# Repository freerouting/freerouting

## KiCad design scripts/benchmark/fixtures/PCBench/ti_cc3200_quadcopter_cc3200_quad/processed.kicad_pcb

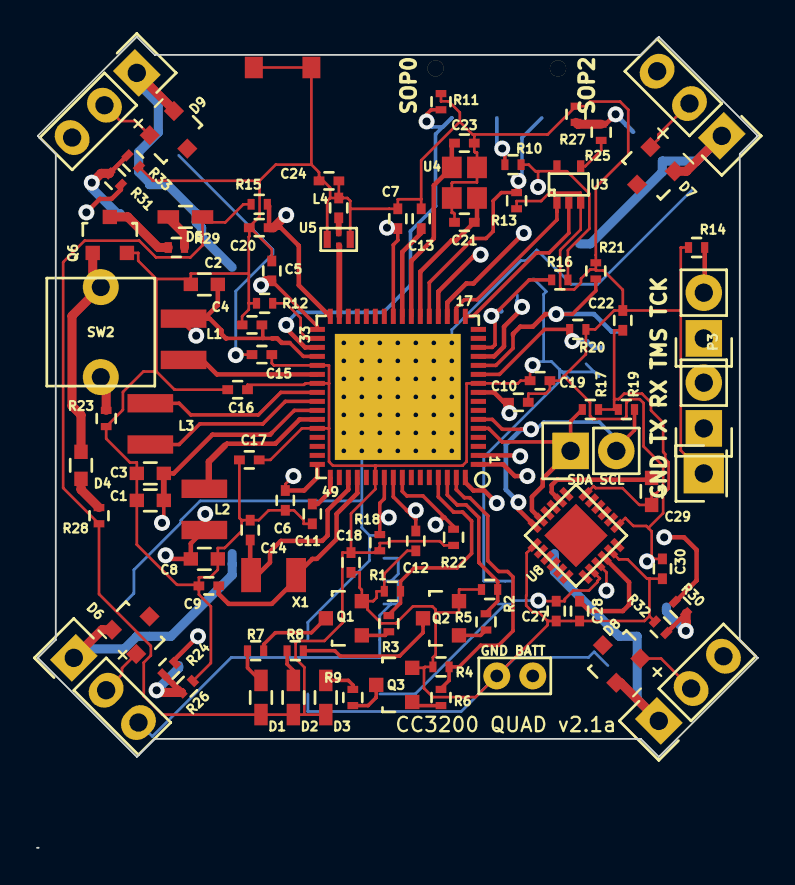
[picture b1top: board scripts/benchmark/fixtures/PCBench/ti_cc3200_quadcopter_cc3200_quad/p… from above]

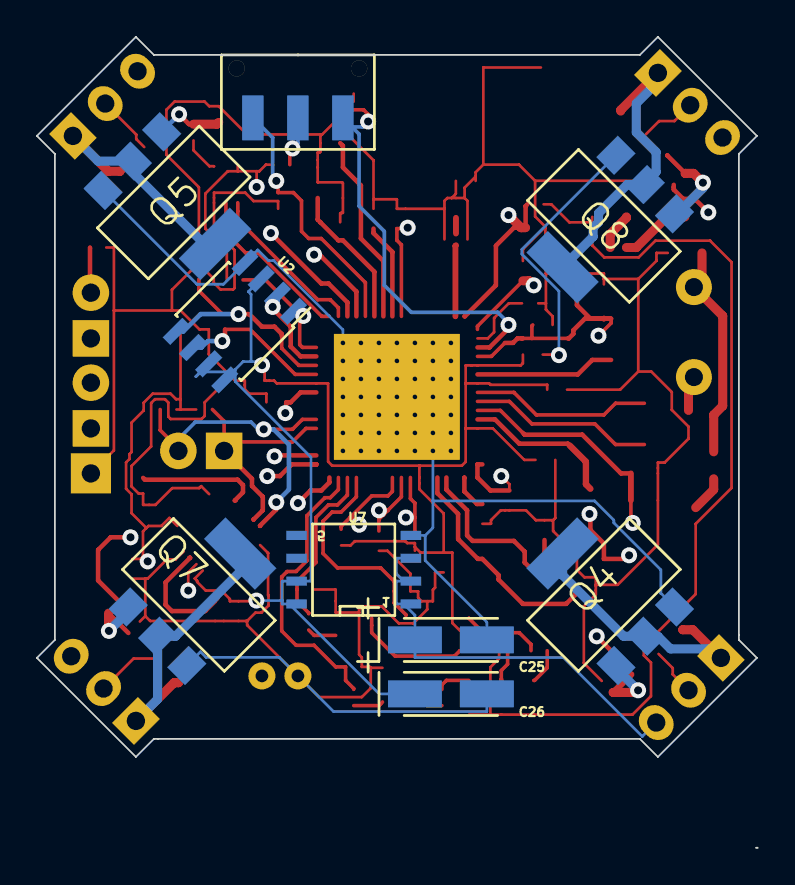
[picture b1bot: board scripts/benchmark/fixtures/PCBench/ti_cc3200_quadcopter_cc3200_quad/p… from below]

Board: 4 copper layers, 40.0 x 40.0 mm, 104 parts (9 on the bottom side), 65 nets.

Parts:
BT1: JST_CONNECTOR; JST_2PIN_2mm
C1, C3: 22uF; C_0603
C2, C8: 10uF; C_0603
C4, C5, C6, C7, C10, C11, C12, C13, C18, C19, C20, C22, C28, C30: 0.1uF; C_0402
C9, C14: 10pF; C_0402
C15, C16, C17: 4.7uF; C_0402
C21, C23: 6.2pF; C_0402
C24: 1.0pF; C_0402
C25, C26: 100uF; TantalC_SizeA_EIA-3216_HandSoldering
C27: 10nF; C_0402
C29: 2.2nF; C_0603
D1, D2, D3, D5: LED; C_0603_HandSoldering
D4: CD0603-B00340; C_0603
D6, D7, D8, D9: BAT54; SOT-23
L1, L2: 2.2uH; Neosid_Inductor_SM-NE29_SMD1008
L3: 1uH; Neosid_Inductor_SM-NE29_SMD1008
L4: 3.6nH; C_0402
M1, M2, M3, M4: DC_Motor; Pin_Header_Straight_1x03
P1, P2, P3: CONN_01X02; Pin_Header_Straight_1x02
P4: CONN_01X01; Pin_Header_Straight_1x01
Q1, Q2, Q3, Q6: BSS138; SOT-23
Q4, Q5, Q7, Q8: BUK9832; SOT-223
R1, R2, R4, R11, R12, R14, R15, R16, R18, R20, R21, R22, R28: 100k; R_0402
R3, R5, R6: 10k; R_0402
R7, R8, R9, R10, R29: 270; R_0402
R13: 2.7k; R_0402
R17, R19: 1k; R_0402
R23: 100; R_0402
R24, R25, R30, R31: 150; R_0402
R26, R27, R32, R33: 1.5k; R_0402
SW1: SWITCH_INV; JS102011SAQN
SW2: EVQ11; EVQ11_Push_Switch
U1: CC3200; cc3200
U2: MX25V8006E; SOIC-8_3.9x4.9mm_Pitch1.27mm
U3: SN74AUP1T08; sc70-5
U4: Q24FA20H00396_40MHz; Q24FA20H
U5: DEA202450BT-1294C1-H; DEA202450BT
U6: AH316M245001; AH316M
U7: MCP1726; SOIC-8-N
U8: MPU6050; MPU-6050
X1: 32.768KHz; ABS07

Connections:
+3.3V: C15.1, C16.1, C17.1, C18.1, C19.1, C22.1, C26.1, C27.1, C30.1, D1.1, D2.1, D3.1, D5.1, R10.1, R15.1, R16.1, R17.1, R18.1, R19.1, R22.1, R28.1, U1.10, U1.37, U1.39, U1.44, U1.54, U2.3, U2.7, U2.8, U3.5, U7.7, U7.8, U8.8, U8.13
+BATT: BT1.1, C25.1, D6.2, D7.2, D8.2, D9.2, M1.2, M2.2, M3.2, M4.2, U7.1, U7.2, U7.3
/LED_1: R1.2, R3.2, U1.61
/LED_2: R2.2, R5.2, U1.62
/LED_3: R4.2, R6.2, U1.63
/Motor_PWM01: R24.2, U1.1
/Motor_PWM02: R30.2, U1.2
/Motor_PWM03: R25.2, U3.4
/Motor_PWM04: R31.2, U1.64
/cc3200_camera_RF/RF: U1.31, U5.1
/cc3200_quad_accel/SCL: P1.1, R17.2, U1.5, U8.23
/cc3200_quad_accel/SDA: P1.2, R19.2, U1.6, U8.24
/rx: P3.2, R22.2, U1.57
/tx: P3.1, R18.2, U1.55
/~Reset: C20.1, D4.2, Q6.1, R15.2, SW2.2, U1.32
GND: BT1.2, C1.2, C2.2, C3.2, C4.2, C5.2, C6.2, C7.2, C8.2, C9.2, C10.2, C11.2, C12.2, C13.2, C14.2, C15.2, C16.2, C17.2, C18.2, C19.2, C20.2, C21.2, C22.2, C23.2, C24.1, C24.2, C25.2, C26.2, C27.2, C28.2, C29.1, C30.2, L4.2, P4.1, Q1.2, Q2.2, Q3.2, Q4.3, Q5.3, Q6.2, Q7.3, Q8.3, R1.1, R2.1, R4.1, R11.2, R12.2, R13.2, R14.1, R20.1, R21.1, R23.2, R26.1, R27.1, R32.1, R33.1, U1.65, U2.4, U3.3, U4.2, U4.4, U5.2, U5.4, U6.1, U6.2, U7.4, U8.1, U8.9, U8.11, U8.18
unnamed: C1.1, C3.1, C5.1, U1.33, U1.42
unnamed: C2.1, C4.1, C6.1, C7.1, L1.1, U1.25, U1.36, U1.48
unnamed: C9.1, U1.52, X1.2
unnamed: C8.1, C10.1, C12.1, L2.1, U1.9, U1.56
unnamed: C11.1, U1.49
unnamed: C13.1, U1.24
unnamed: C14.1, U1.51, X1.1
unnamed: C21.1, U1.22, U4.3
unnamed: C23.1, U1.23, U4.1
unnamed: C28.1, U8.10
unnamed: C29.2, U8.20
unnamed: D1.2, R7.1
unnamed: D2.2, R8.1
unnamed: D3.2, R9.1
unnamed: D4.1, R28.2
unnamed: D5.2, R29.1
unnamed: D6.1, M1.1, Q4.2
unnamed: D7.1, M2.1, Q5.2
unnamed: D8.1, M3.1, Q7.2
unnamed: D9.1, M4.1, Q8.2
unnamed: L1.2, U1.38
unnamed: L2.2, U1.43
unnamed: L3.1, U1.41
unnamed: L3.2, U1.40
unnamed: L4.1, U5.3
unnamed: P2.1, U1.20
unnamed: P2.2, R14.2, U1.19
unnamed: Q1.1, R3.1
unnamed: Q1.3, R7.2
unnamed: Q2.1, R5.1
unnamed: Q2.3, R8.2
unnamed: Q3.1, R6.1
unnamed: Q3.3, R9.2
unnamed: Q4.1, R24.1, R26.2
unnamed: Q5.1, R25.1, R27.2
unnamed: Q6.3, R29.2
unnamed: Q7.1, R30.1, R32.2
unnamed: Q8.1, R31.1, R33.2
unnamed: R10.2, SW1.2
unnamed: R11.1, SW1.1, U1.35
unnamed: R12.1, U1.34
unnamed: R13.1, SW1.3, U1.21
unnamed: R16.2, U1.14, U2.1
unnamed: R20.2, U1.11, U2.6
unnamed: R21.2, U1.12, U2.5
unnamed: R23.1, SW2.1
unnamed: U1.13, U2.2
unnamed: U1.17, U3.2
unnamed: U1.18, U3.1

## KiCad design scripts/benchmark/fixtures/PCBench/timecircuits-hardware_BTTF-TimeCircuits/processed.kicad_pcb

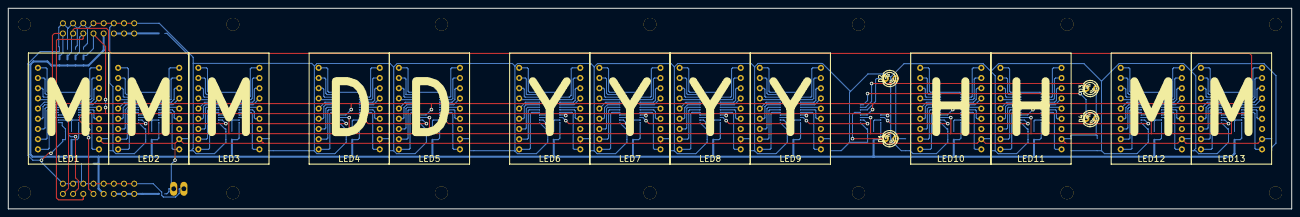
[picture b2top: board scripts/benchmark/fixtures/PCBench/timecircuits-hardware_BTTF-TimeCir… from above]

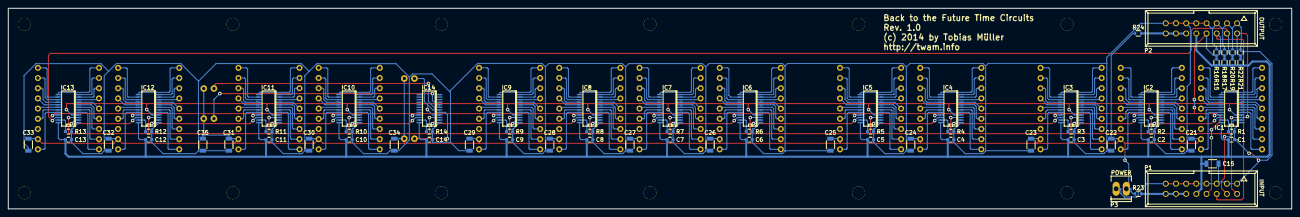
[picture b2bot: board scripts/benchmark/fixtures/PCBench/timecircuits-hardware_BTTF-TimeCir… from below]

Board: 2 copper layers, 320.0 x 50.0 mm, 102 parts (71 on the bottom side), 249 nets.

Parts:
C1, C2, C3, C4, C5, C6, C7, C8, C9, C10, C11, C12, C13, C14: C; C_0603
C15, C21, C22, C23, C24, C25, C26, C27, C28, C29, C30, C31, C32, C33, C34, C35: CP2; C_1206
D1, D2, D3, D4: LED; LED-3MM
IC1, IC2, IC3, IC4, IC5, IC6, IC7, IC8, IC9, IC10, IC11, IC12, IC13, IC14: TLC59284; SSOP-24
LED1, LED2, LED3, LED4, LED5, LED6, LED7, LED8, LED9, LED10, LED11, LED12, LED13: PSA08-11
MOUNTING_HOLE_3-2MM_M3, MOUNTING_HOLE_3-2MM_M3_2, MOUNTING_HOLE_3-2MM_M3_3, MOUNTING_HOLE_3-2MM_M3_4, MOUNTING_HOLE_3-2MM_M3_5, MOUNTING_HOLE_3-2MM_M3_6, MOUNTING_HOLE_3-2MM_M3_7, MOUNTING_HOLE_3-2MM_M3_8, MOUNTING_HOLE_3-2MM_M3_9, MOUNTING_HOLE_3-2MM_M3_10, MOUNTING_HOLE_3-2MM_M3_11, MOUNTING_HOLE_3-2MM_M3_12, MOUNTING_HOLE_3-2MM_M3_13, MOUNTING_HOLE_3-2MM_M3_14: VAL**; MOUNTING_HOLE_3-2MM_M3
P1: INPUT; VASCH8x2
P2: OUTPUT; VASCH8x2
P3: POWER; Socket_MOLEX-KK-RM2-54mm_Lock_2pin_straight
R1, R2, R3, R4, R5, R6, R7, R8, R9, R10, R11, R12, R13, R14: R; C_0603
R15, R16, R17, R18, R19, R20, R21, R22, R23, R24: R; R_0603

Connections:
+5V: C21.1, C22.1, C23.1, C24.1, C25.1, C26.1, C27.1, C28.1, C29.1, C30.1, C31.1, C32.1, C33.1, C34.1, C35.1, D1.1, D2.1, D3.1, D4.1, LED1.11, LED2.11, LED3.11, LED4.11, LED5.11, LED6.11, LED7.11, LED8.11, LED9.11, LED10.11, LED11.11, LED12.11, LED13.11, P3.1, R23.2, R24.2
/A1: IC1.13, LED1.1
/A2: IC2.13, LED2.1
/A3: IC3.13, LED3.1
/A4: IC4.13, LED4.1
/A5: IC5.13, LED5.1
/A6: IC6.13, LED6.1
/A7: IC7.13, LED7.1
/A8: IC8.13, LED8.1
/A9: IC9.13, LED9.1
/A10: IC10.13, LED10.1
/A11: IC11.13, LED11.1
/A12: IC12.13, LED12.1
/A13: IC13.13, LED13.1
/B1: IC1.14, LED1.18
/B2: IC2.14, LED2.18
/B3: IC3.14, LED3.18
/B4: IC4.14, LED4.18
/B5: IC5.14, LED5.18
/B6: IC6.14, LED6.18
/B7: IC7.14, LED7.18
/B8: IC8.14, LED8.18
/B9: IC9.14, LED9.18
/B10: IC10.14, LED10.18
/B11: IC11.14, LED11.18
/B12: IC12.14, LED12.18
/B13: IC13.14, LED13.18
/BLK: IC1.21, IC2.21, IC3.21, IC4.21, IC5.21, IC6.21, IC7.21, IC8.21, IC9.21, IC10.21, IC11.21, IC12.21, IC13.21, IC14.21, P1.8, P2.8, R15.2, R16.1
/C1: IC1.16, LED1.16
/C2: IC2.16, LED2.16
/C3: IC3.16, LED3.16
/C4: IC4.16, LED4.16
/C5: IC5.16, LED5.16
/C6: IC6.16, LED6.16
/C7: IC7.16, LED7.16
/C8: IC8.16, LED8.16
/C9: IC9.16, LED9.16
/C10: IC10.16, LED10.16
/C11: IC11.16, LED11.16
/C12: IC12.16, LED12.16
/C13: IC13.16, LED13.16
/D1: IC1.19, LED1.13
/D2: IC2.19, LED2.13
/D3: IC3.19, LED3.13
/D4: IC4.19, LED4.13
/D5: IC5.19, LED5.13
/D6: IC6.19, LED6.13
/D7: IC7.19, LED7.13
/D8: IC8.19, LED8.13
/D9: IC9.19, LED9.13
/D10: IC10.19, LED10.13
/D11: IC11.19, LED11.13
/D12: IC12.19, LED12.13
/D13: IC13.19, LED13.13
/DATA_IN: IC1.2, P1.4
/DATA_OUT: IC13.22, P2.4, R19.2, R20.1
/E1: IC1.20, LED1.10
/E2: IC2.20, LED2.10
/E3: IC3.20, LED3.10
/E4: IC4.20, LED4.10
/E5: IC5.20, LED5.10
/E6: IC6.20, LED6.10
/E7: IC7.20, LED7.10
/E8: IC8.20, LED8.10
/E9: IC9.20, LED9.10
/E10: IC10.20, LED10.10
/E11: IC11.20, LED11.10
/E12: IC12.20, LED12.10
/E13: IC13.20, LED13.10
/F1: IC1.5, LED1.9
/F2: IC2.5, LED2.9
/F3: IC3.5, LED3.9
/F4: IC4.5, LED4.9
/F5: IC5.5, LED5.9
/F6: IC6.5, LED6.9
/F7: IC7.5, LED7.9
/F8: IC8.5, LED8.9
/F9: IC9.5, LED9.9
/F10: IC10.5, LED10.9
/F11: IC11.5, LED11.9
/F12: IC12.5, LED12.9
/F13: IC13.5, LED13.9
/G1: IC1.6, LED1.8
/G2: IC2.6, LED2.8
/G3: IC3.6, LED3.8
/G4: IC4.6, LED4.8
/G5: IC5.6, LED5.8
/G6: IC6.6, LED6.8
/G7: IC7.6, LED7.8
/G8: IC8.6, LED8.8
/G9: IC9.6, LED9.8
/G10: IC10.6, LED10.8
/G11: IC11.6, LED11.8
/G12: IC12.6, LED12.8
/G13: IC13.6, LED13.8
/H1: IC1.10, LED1.4
/H2: IC2.10, LED2.4
/H3: IC3.10, LED3.4
/H4: IC4.10, LED4.4
/H5: IC5.10, LED5.4
/H6: IC6.10, LED6.4
/H7: IC7.10, LED7.4
/H8: IC8.10, LED8.4
/H9: IC9.10, LED9.4
/H10: IC10.10, LED10.4
/H11: IC11.10, LED11.4
/H12: IC12.10, LED12.4
/H13: IC13.10, LED13.4
/K1: IC1.11, LED1.3
/K2: IC2.11, LED2.3
/K3: IC3.11, LED3.3
/K4: IC4.11, LED4.3
/K5: IC5.11, LED5.3
/K6: IC6.11, LED6.3
/K7: IC7.11, LED7.3
/K8: IC8.11, LED8.3
/K9: IC9.11, LED9.3
/K10: IC10.11, LED10.3
/K11: IC11.11, LED11.3
/K12: IC12.11, LED12.3
/K13: IC13.11, LED13.3
/LAT: IC1.4, IC2.4, IC3.4, IC4.4, IC5.4, IC6.4, IC7.4, IC8.4, IC9.4, IC10.4, IC11.4, IC12.4, IC13.4, IC14.4, P1.6, P2.6, R17.2, R18.1
/M1: IC1.12, LED1.2
/M2: IC2.12, LED2.2
/M3: IC3.12, LED3.2
/M4: IC4.12, LED4.2
/M5: IC5.12, LED5.2
/M6: IC6.12, LED6.2
/M7: IC7.12, LED7.2
/M8: IC8.12, LED8.2
/M9: IC9.12, LED9.2
/M10: IC10.12, LED10.2
/M11: IC11.12, LED11.2
/M12: IC12.12, LED12.2
/M13: IC13.12, LED13.2
/N1: IC1.15, LED1.17
/N2: IC2.15, LED2.17
/N3: IC3.15, LED3.17
/N4: IC4.15, LED4.17
/N5: IC5.15, LED5.17
/N6: IC6.15, LED6.17
/N7: IC7.15, LED7.17
/N8: IC8.15, LED8.17
/N9: IC9.15, LED9.17
/N10: IC10.15, LED10.17
/N11: IC11.15, LED11.17
/N12: IC12.15, LED12.17
/N13: IC13.15, LED13.17
/P1: IC1.17, LED1.15
/P2: IC2.17, LED2.15
/P3: IC3.17, LED3.15
/P4: IC4.17, LED4.15
/P5: IC5.17, LED5.15
/P6: IC6.17, LED6.15
/P7: IC7.17, LED7.15
/P8: IC8.17, LED8.15
/P9: IC9.17, LED9.15
/P10: IC10.17, LED10.15
/P11: IC11.17, LED11.15
/P12: IC12.17, LED12.15
/P13: IC13.17, LED13.15
/R1: IC1.18, LED1.14
/R2: IC2.18, LED2.14
/R3: IC3.18, LED3.14
/R4: IC4.18, LED4.14
/R5: IC5.18, LED5.14
/R6: IC6.18, LED6.14
/R7: IC7.18, LED7.14
/R8: IC8.18, LED8.14
/R9: IC9.18, LED9.14
/R10: IC10.18, LED10.14
/R11: IC11.18, LED11.14
/R12: IC12.18, LED12.14
/R13: IC13.18, LED13.14
/S1: IC1.8, LED1.6
/S2: IC2.8, LED2.6
/S3: IC3.8, LED3.6
/S4: IC4.8, LED4.6
/S5: IC5.8, LED5.6
/S6: IC6.8, LED6.6
/S7: IC7.8, LED7.6
/S8: IC8.8, LED8.6
/S9: IC9.8, LED9.6
/S10: IC10.8, LED10.6
/S11: IC11.8, LED11.6
/S12: IC12.8, LED12.6
/S13: IC13.8, LED13.6
/SCLK: IC1.3, IC2.3, IC3.3, IC4.3, IC5.3, IC6.3, IC7.3, IC8.3, IC9.3, IC10.3, IC11.3, IC12.3, IC13.3, IC14.3, P1.2, P2.2, R21.2, R22.1
/T1: IC1.7, LED1.7
/T2: IC2.7, LED2.7
/T3: IC3.7, LED3.7
/T4: IC4.7, LED4.7
/T5: IC5.7, LED5.7
/T6: IC6.7, LED6.7
/T7: IC7.7, LED7.7
/T8: IC8.7, LED8.7
/T9: IC9.7, LED9.7
/T10: IC10.7, LED10.7
/T11: IC11.7, LED11.7
/T12: IC12.7, LED12.7
/T13: IC13.7, LED13.7
/U1: IC1.9, LED1.5
/U2: IC2.9, LED2.5
/U3: IC3.9, LED3.5
/U4: IC4.9, LED4.5
/U5: IC5.9, LED5.5
/U6: IC6.9, LED6.5
/U7: IC7.9, LED7.5
/U8: IC8.9, LED8.5
/U9: IC9.9, LED9.5
/U10: IC10.9, LED10.5
/U11: IC11.9, LED11.5
/U12: IC12.9, LED12.5
/U13: IC13.9, LED13.5
GND: C1.2, C2.2, C3.2, C4.2, C5.2, C6.2, C7.2, C8.2, C9.2, C10.2, C11.2, C12.2, C13.2, C14.2, C15.2, C21.2, C22.2, C23.2, C24.2, C25.2, C26.2, C27.2, C28.2, C29.2, C30.2, C31.2, C32.2, C33.2, C34.2, C35.2, IC1.1, IC2.1, IC3.1, IC4.1, IC5.1, IC6.1, IC7.1, IC8.1, IC9.1, IC10.1, IC11.1, IC12.1, IC13.1, IC14.1, P1.1, P1.3, P1.5, P1.7, P1.9, P1.11, P1.13, P1.15, P2.1, P2.3, P2.5, P2.7, P2.9, P2.11, P2.13, P2.15, P3.2, R1.2, R2.2, R3.2, R4.2, R5.2, R6.2, R7.2, R8.2, R9.2, R10.2, R11.2, R12.2, R13.2, R14.2, R16.2, R18.2, R20.2, R22.2
unnamed: D1.2, IC14.5
unnamed: D2.2, IC14.6
unnamed: D3.2, IC14.7
unnamed: D4.2, IC14.8
unnamed: IC1.22, IC2.2
unnamed: IC1.23, R1.1
unnamed: IC2.22, IC3.2
unnamed: IC2.23, R2.1
unnamed: IC3.22, IC4.2
unnamed: IC3.23, R3.1
unnamed: IC4.22, IC5.2
unnamed: IC4.23, R4.1
unnamed: IC5.22, IC6.2
unnamed: IC5.23, R5.1
unnamed: IC6.22, IC7.2
unnamed: IC6.23, R6.1
unnamed: IC7.22, IC8.2
unnamed: IC7.23, R7.1
unnamed: IC8.22, IC9.2
unnamed: IC8.23, R8.1
unnamed: IC9.23, R9.1
unnamed: IC10.2, IC14.22
unnamed: IC10.22, IC11.2
unnamed: IC10.23, R10.1
unnamed: IC11.22, IC12.2
unnamed: IC11.23, R11.1
unnamed: IC12.22, IC13.2
unnamed: IC12.23, R12.1
unnamed: IC13.23, R13.1
unnamed: IC9.22, IC14.2
unnamed: IC14.23, R14.1
unnamed: P1.12, P1.14, P1.16, R23.1
unnamed: P2.12, P2.14, P2.16, R24.1
VCC: C1.1, C2.1, C3.1, C4.1, C5.1, C6.1, C7.1, C8.1, C9.1, C10.1, C11.1, C12.1, C13.1, C14.1, C15.1, IC1.24, IC2.24, IC3.24, IC4.24, IC5.24, IC6.24, IC7.24, IC8.24, IC9.24, IC10.24, IC11.24, IC12.24, IC13.24, IC14.24, P1.10, P2.10, R15.1, R17.1, R19.1, R21.1

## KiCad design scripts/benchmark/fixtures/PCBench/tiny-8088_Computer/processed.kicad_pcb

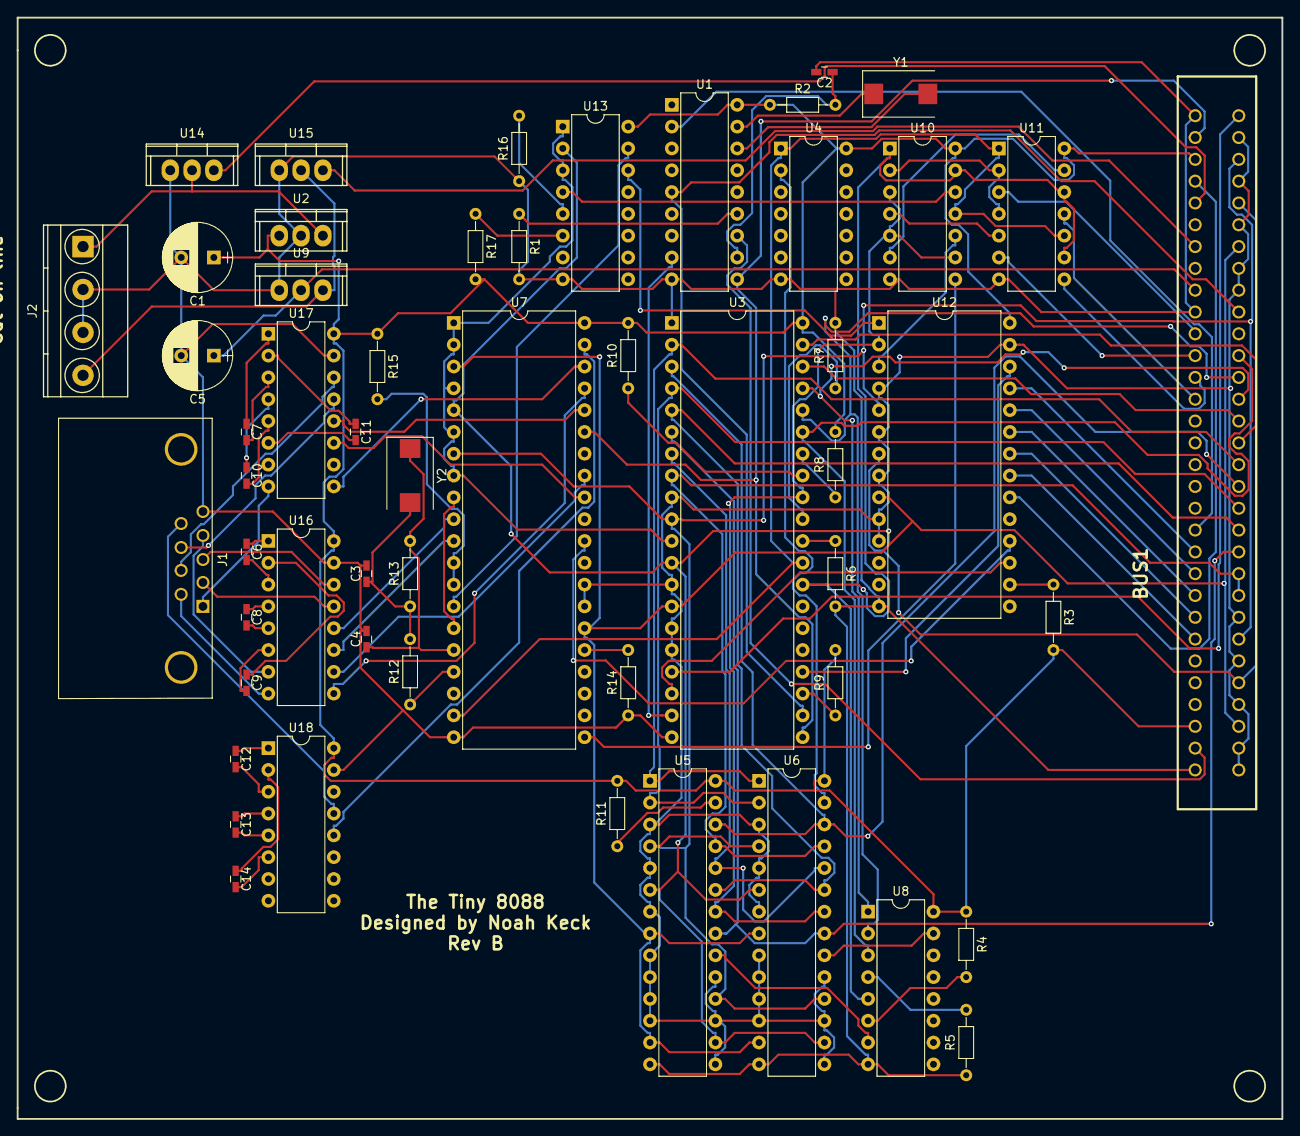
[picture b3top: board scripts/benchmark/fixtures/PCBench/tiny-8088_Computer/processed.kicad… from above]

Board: 2 copper layers, 147.3 x 128.3 mm, 54 parts (0 on the bottom side), 111 nets.

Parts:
BUS1: BUSPC; ISA8
C1, C5: 10 uF; CP_Radial_D8.0mm_P3.80mm
C2: 1n; C_0603_HandSoldering
C3, C4: 10 pF; C_0603_HandSoldering
C6, C7, C8, C9, C10, C11, C12, C13, C14: 1 uF; C_0603_HandSoldering
J1: DB9; DB9FC
J2: Screw_Terminal_1x04; TerminalBlock_Pheonix_MKDS1.5-4pol
R1, R3, R4, R5, R6, R7, R8, R9, R10, R11, R14, R15, R16, R17: 10k; R_Axial_DIN0204_L3.6mm_D1.6mm_P7.62mm_Horizontal
R2: 1k; R_Axial_DIN0204_L3.6mm_D1.6mm_P7.62mm_Horizontal
R12, R13: 2.2k; R_Axial_DIN0204_L3.6mm_D1.6mm_P7.62mm_Horizontal
U1: 8284; DIP-18_W7.62mm
U2: LM2931AZ-5.0; TO-220
U3: 8088; DIP-40_W15.24mm
U4, U10: 74LS04; DIP-14_W7.62mm
U5: 28C256; DIP-28_W7.62mm
U6: RAM_32KO; DIP-28_W7.62mm
U7: 16450; DIP-40_W15.24mm
U8, U13: 74LS138; DIP-16_W7.62mm
U9: NCP1117DT12G; TO-220
U11: 7400; DIP-14_W7.62mm
U12: 8259; DIP-28_W15.24mm
U14: LM7905CT; TO-220
U15: LM7912CT; TO-220
U16, U17, U18: MAX202; DIP-16_W7.62mm
Y1: 8 MHz; Crystal_SMD_FOX_FE-2pin_7.5x5.0mm
Y2: 3.072 MHz; Crystal_SMD_FOX_FE-2pin_7.5x5.0mm

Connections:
A0: BUS1.33, BUS1.35, BUS1.37, BUS1.39, BUS1.40, BUS1.55, BUS1.57, BUS1.59, BUS1.61, BUS1.62, U3.9, U3.11, U3.13, U3.15, U3.16, U5.3, U5.5, U5.7, U5.9, U5.10, U5.11, U5.12, U5.15, U5.17, U5.19, U6.3, U6.5, U6.7, U6.9, U6.10, U6.11, U6.12, U6.15, U6.17, U6.19, U7.1, U7.2, U7.4, U7.6, U7.8, U7.27, U7.28, U12.4, U12.6, U12.8, U12.10, U12.11, U12.27, U13.1, U13.3
A2: BUS1.38, BUS1.60, U3.14, U5.8, U5.13, U6.8, U6.13, U7.3, U7.26, U12.9
A4: BUS1.36, BUS1.58, U3.12, U5.6, U5.16, U6.6, U6.16, U7.5, U12.7, U13.2
A6: BUS1.34, BUS1.56, U3.10, U5.4, U5.18, U6.4, U6.18, U7.7, U12.5
A8: BUS1.53, BUS1.54, U3.8, U5.25, U6.25
A10: BUS1.52, U3.6, U5.21, U6.21
A11: BUS1.51, U3.5, U5.23, U6.23
A12: BUS1.50, U3.4, U5.2, U6.2
A13: BUS1.49, U3.3, U5.26, U6.26
A14: BUS1.48, U3.2, U5.1, U6.1
A15: BUS1.47, U3.39
A16: BUS1.46, U3.38
A17: BUS1.45, U3.37, U8.1
A18: BUS1.44, U3.36, U8.2
A19: BUS1.43, U3.35, U8.3
GND: BUS1.1, BUS1.10, BUS1.31, C1.2, C2.2, C3.2, C4.2, C5.2, J1.5, J2.2, J2.3, R1.2, R5.1, R6.2, R7.2, R14.1, R16.1, U1.9, U2.2, U3.1, U3.20, U4.7, U5.14, U6.14, U7.20, U8.8, U9.1, U10.7, U11.7, U12.14, U13.8, U14.1, U15.1, U16.15, U17.15, U18.15
INT: U3.18, U12.17
INTA: U3.24, U12.26
IO/M: U3.28, U8.5, U10.1, U10.13, U11.9, U11.12
IRQ0: U7.30, U12.18
unnamed: BUS1.2, U1.10, U3.21, U7.35
unnamed: BUS1.4, U12.20
unnamed: BUS1.5, U14.3
unnamed: BUS1.7, U15.3
unnamed: BUS1.9, C5.1, U9.2
unnamed: BUS1.11, U11.3
unnamed: BUS1.12, U11.6
unnamed: BUS1.13, U11.8
unnamed: BUS1.14, U11.11
unnamed: BUS1.20, U1.2
unnamed: BUS1.21, U12.25
unnamed: BUS1.22, U12.24
unnamed: BUS1.23, U12.23
unnamed: BUS1.24, U12.22
unnamed: BUS1.25, U12.21
unnamed: BUS1.30, U1.12
unnamed: BUS1.32, U3.17
unnamed: BUS1.41, U1.5, U3.22
unnamed: C2.1, R2.2, U1.11
unnamed: C3.1, R12.2, R13.1, Y2.2
unnamed: C6.1, U16.1
unnamed: C6.2, U16.3
unnamed: C7.1, U17.1
unnamed: C7.2, U17.3
unnamed: C8.1, U16.4
unnamed: C8.2, U16.5
unnamed: C9.1, U16.2
unnamed: C9.2, U16.6
unnamed: C10.1, U17.4
unnamed: C10.2, U17.5
unnamed: C11.1, U17.2
unnamed: C11.2, U17.6
unnamed: C12.1, U18.1
unnamed: C12.2, U18.3
unnamed: C13.1, U18.4
unnamed: C13.2, U18.5
unnamed: C14.1, U18.2
unnamed: C14.2, U18.6
unnamed: J1.1, U17.8
unnamed: J1.2, U16.13
unnamed: J1.3, U16.14
unnamed: J1.4, U16.7
unnamed: J1.6, U16.8
unnamed: J1.7, U17.14
unnamed: J1.8, U17.13
unnamed: J1.9, U18.13
unnamed: J2.1, U2.3, U14.2
unnamed: J2.4, U9.3, U15.2
unnamed: R1.1, U1.13
unnamed: R3.1, U12.16
unnamed: R4.2, U8.6
unnamed: R5.2, U8.4
unnamed: R6.1, U3.30
unnamed: R7.1, U3.31
unnamed: R8.1, U3.34
unnamed: R9.1, U3.23
unnamed: R10.1, U3.33
unnamed: R11.1, U5.27
unnamed: R14.2, U7.25
unnamed: R15.2, U7.12, U7.13
unnamed: R16.2, U13.5
unnamed: R17.1, U13.6
unnamed: U1.8, U3.19
unnamed: U1.16, Y1.2
unnamed: U1.17, Y1.1
unnamed: U3.7, U5.24, U6.24
unnamed: U4.2, U6.27
unnamed: U5.20, U8.7
unnamed: U6.20, U8.15
unnamed: U7.9, U7.15
unnamed: U10.2, U11.2, U11.4
unnamed: U10.4, U11.5
unnamed: U10.6, U11.13
unnamed: U7.21, U10.8
unnamed: U10.10, U12.3
unnamed: U10.12, U13.4
unnamed: U12.1, U13.14
unnamed: U7.14, U13.15
unnamed: U7.37, U16.9
unnamed: U7.33, U16.10
unnamed: U7.11, U16.11
unnamed: U7.10, U16.12
unnamed: U7.38, U17.9
unnamed: U7.32, U17.11
unnamed: U7.36, U17.12
unnamed: U7.39, U18.12
RD: U3.32, U5.22, U6.22, U10.3, U10.5, U10.9, U12.2
SXI: C4.1, R13.2, U7.16, Y2.1
SXO: R12.1, U7.17
Vcc: BUS1.3, BUS1.29, C1.1, R2.1, R3.2, R4.1, R8.2, R9.2, R10.2, R11.2, R15.1, R17.2, U1.18, U2.1, U3.40, U4.14, U5.28, U6.28, U7.40, U8.16, U10.14, U11.14, U12.28, U13.16, U16.16, U17.16, U18.16
WR: U3.29, U4.1, U7.19, U10.11, U11.1, U11.10

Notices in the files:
scripts/benchmark/fixtures/PCBench/timecircuits-hardware_BTTF-TimeCircuits/processed.kicad_pcb:
(c) 2014 by Tobias Müller
